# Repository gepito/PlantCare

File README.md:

# PlantCare

## Hardware and software to implement life sustaining environment for plants

The aim of this project is to be system oriented. Dealing with sensors, actuators, control and providing failsafe concept.

The principles of workflow are

- use comercially available components wherever possible for cost effective implementation
- provide effective means of monitoring the hardware-software-plant ecosystem
- improve the the components limiting the quality of the system - well, we may actually improve hardware and software only :)

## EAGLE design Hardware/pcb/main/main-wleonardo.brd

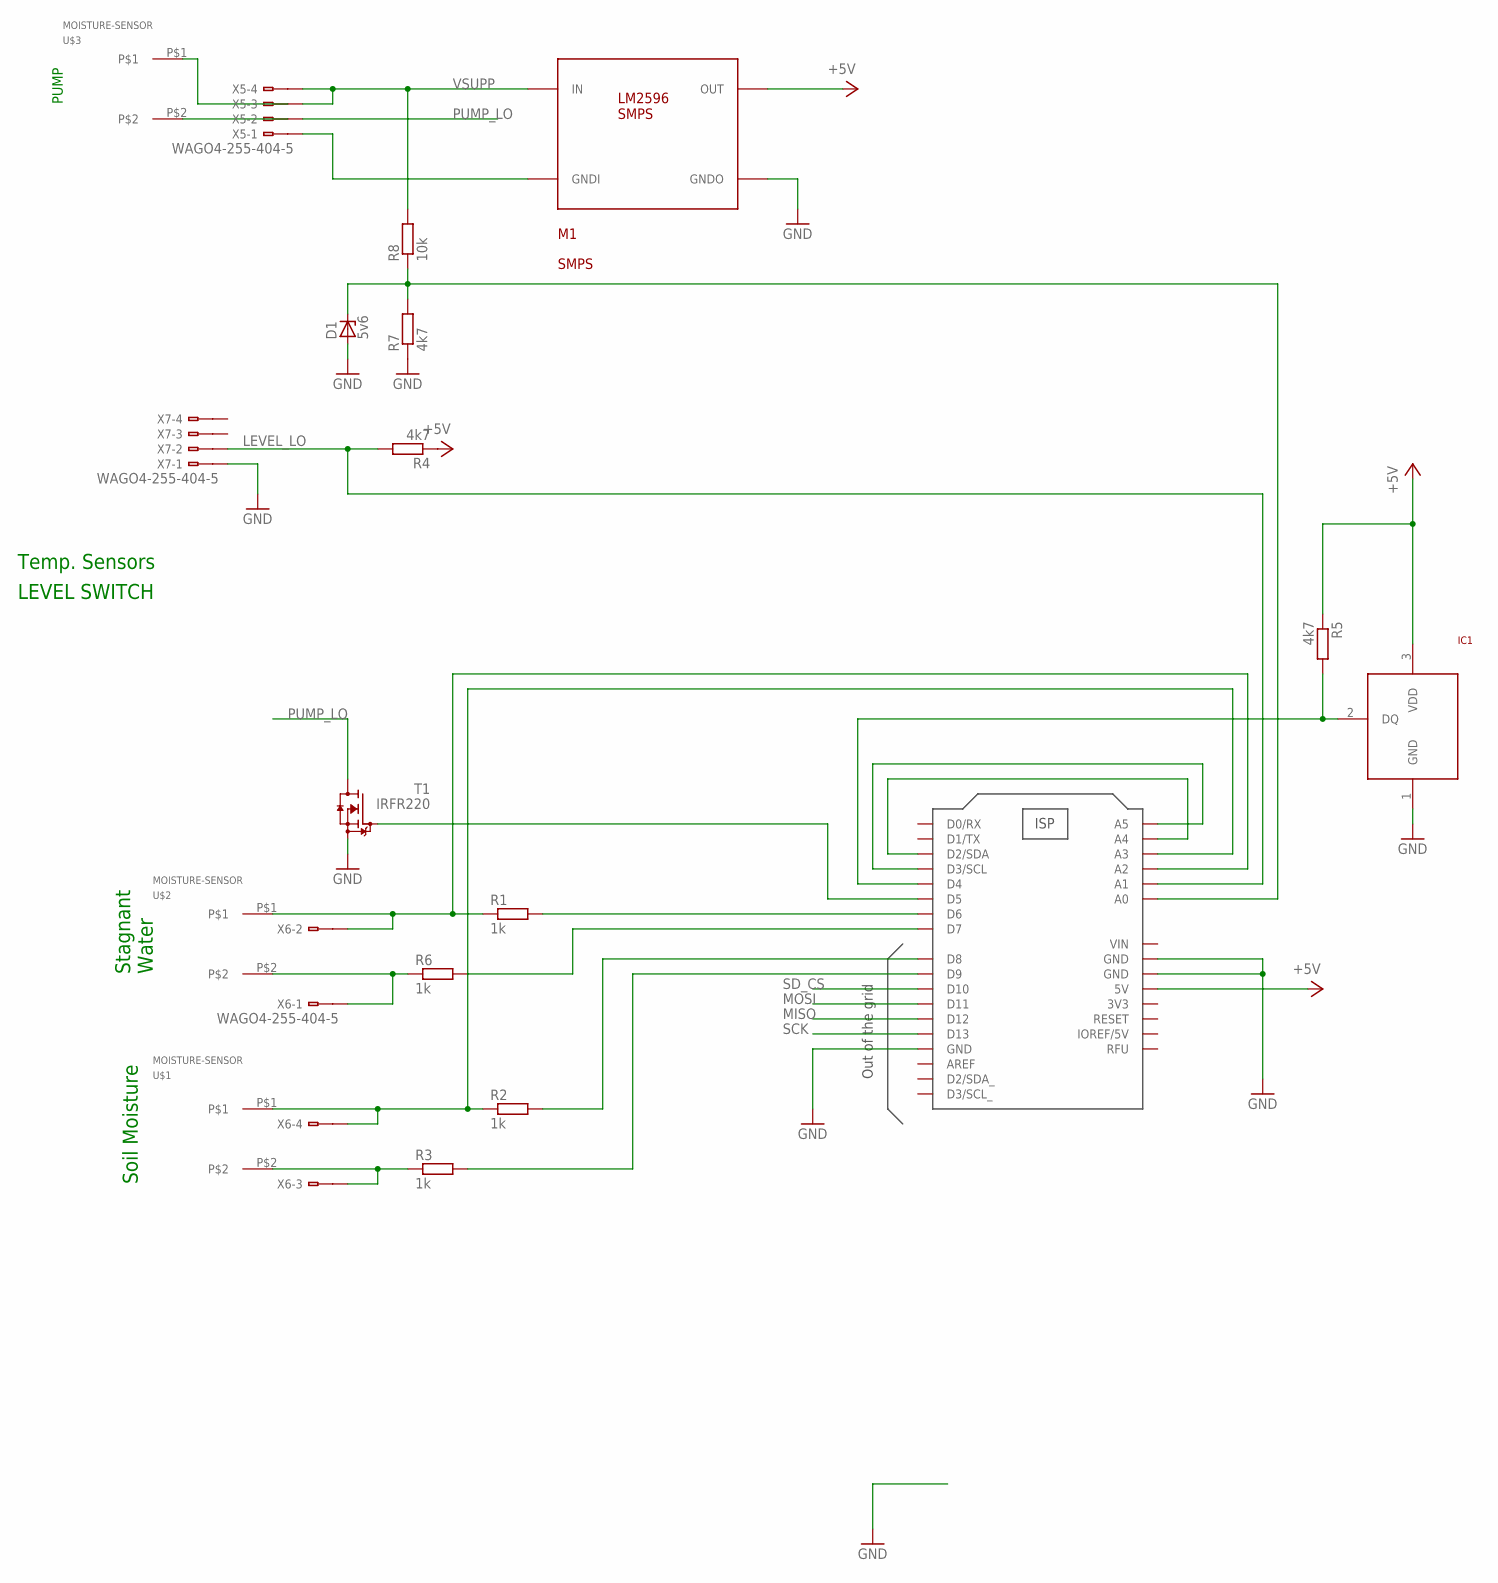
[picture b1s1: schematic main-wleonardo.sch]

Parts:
D1: 5v6; SOT23
IC1: PAPP_DS1820; PAPP_TO92-
LEONARDO: SPARKFUN-BOARDS_ARDUINO-LEONARDO-OUTLINE; SPARKFUN-BOARDS_ARDUINO_R3
M1: SMPS; SMPS-1
R1, R2, R3, R6: 1k; R0805
R4, R5, R7: 4k7; R0805
R8: 10k; R0805
T1: IRFR220; TO252
U$1, U$2, U$3: MOISTURE-SENSOR
X5, X6, X7: WAGO4-255-404-5; 255-404-5

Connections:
1W-DATA: IC1.2 (DQ), LEONARDO.D4, R5.2
+5V: IC1.3 (VDD), LEONARDO.5V, M1.P$7 (OUT), M1.P$8 (OUT), R4.1, R5.1
GND: D1.1 (A), IC1.1 (GND), LEONARDO.GND@1 (GND), LEONARDO.GND@2 (GND), LEONARDO.GND@3 (GND), M1.P$5 (GNDO), M1.P$6 (GNDO), R7.1, T1.2 (S), X7.B1
LEVEL_LO: LEONARDO.A1, R4.2, X7.B2 (B1)
MISO: LEONARDO.D12
MOSI: LEONARDO.D11
unnamed: LEONARDO.D5, T1.1 (G)
unnamed: M1.P$1 (GNDI), M1.P$2 (GNDI), X5.B1
unnamed: R6.1, U$2.P$2, X6.B1
unnamed: LEONARDO.D6, R1.2
unnamed: D1.3 (C), LEONARDO.A0, R7.2, R8.1
unnamed: R3.1, U$1.P$2, X6.B3 (B1)
unnamed: U$3.P$2, X5.A2 (A1)
unnamed: U$3.P$1, X5.A3 (A1)
unnamed: LEONARDO.A2, R1.1, U$2.P$1, X6.B2 (B1)
unnamed: LEONARDO.D7, R6.2
unnamed: LEONARDO.A3, R2.1, U$1.P$1, X6.B4 (B1)
unnamed: LEONARDO.D9, R3.2
unnamed: LEONARDO.A4, LEONARDO.D2 (D2/SDA)
unnamed: LEONARDO.A5, LEONARDO.D3 (D3/SCL)
unnamed: LEONARDO.D8, R2.2
PUMP_LO: T1.3 (D), X5.B2 (B1)
SCK: LEONARDO.D13
SD_CS: LEONARDO.D10
VSUPP: M1.P$3 (IN), M1.P$4 (IN), R8.2, X5.B3 (B1), X5.B4 (B1)

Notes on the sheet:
Soil Moisture
LEVEL SWITCH
Temp. Sensors
Stagnant Water
PUMP

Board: 2 copper layers, 19 parts (0 on the bottom side), 21 nets, no tracks yet.

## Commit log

2020-08-20 Files imported from local working directory
2020-08-20 Measurement renamed, nem measurement added
2020-09-27 new measurement file
2020-09-27 Delete DATA-20200820.TXT
    included in DATA-20200927 file
2020-11-01 Plotting scripts added
    Irrelevant scripts deleted
    House heat-up data added with plot
2021-04-06 Oxrat sketch added
2024-06-01 measurements added
    - hardware serial interface
    - improve operation
2024-06-08 Moisture level adjusted
    Header has timestamp at startup
    Serial input exhaust
2025-11-23 data consolidation
    data caption added
2025-11-23 serial debug output added
2025-11-23 data consolidation
2025-11-23 documentation added
2025-11-23 Revise caption.md to use markdown table format
    Updated the formatting of the caption table for clarity.
2025-12-04 new todo item
2025-12-14 space separated files added
    python csv reader example
